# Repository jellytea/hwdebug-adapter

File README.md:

# hwdebug-adapter
Adapter for various debug ports.

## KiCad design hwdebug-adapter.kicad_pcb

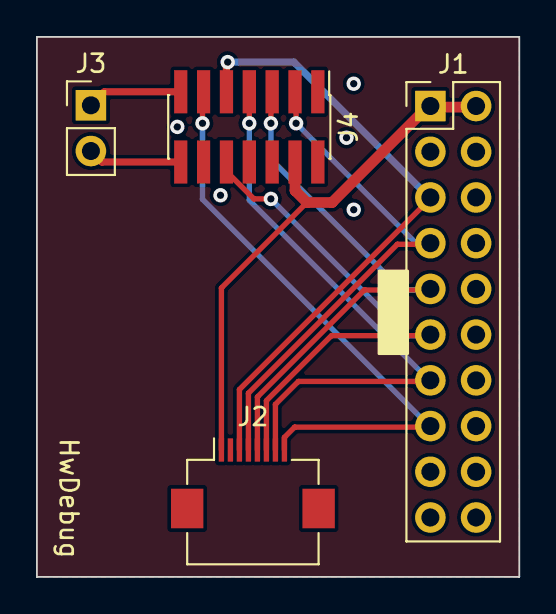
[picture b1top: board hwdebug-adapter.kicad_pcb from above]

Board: 2 copper layers, 26.8 x 30.0 mm, 4 parts (0 on the bottom side), 10 nets.

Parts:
J1: Conn_ARM_JTAG_SWD_20; PinHeader_2x10_P2.54mm_Vertical
J2: Conn_01x08_MountingPin; Hirose_FH12-8S-0.5SH_1x08-1MP_P0.50mm_Horizontal
J3: Conn_01x02; PinHeader_1x02_P2.54mm_Vertical
J4: Conn_ST_STDC14; PinHeader_2x07_P1.27mm_Vertical_SMD

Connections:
+3V3: J1.1 (VTREF), J1.2 (VCC/NC), J2.1, J4.3 (VCC)
GND: J1.4 (GND), J1.6 (GND), J1.8 (GND), J1.10 (GND), J1.12 (GND), J1.14 (GND), J1.16 (GND), J1.18 (GND), J1.20 (GND), J2.2, J2.MP (MountPin), J4.5 (GND), J4.7 (GND), J4.11 (GNDDetect)
unnamed: J1.11 (RTCK), J2.6, J4.9 (JRCLK/NC)
unnamed: J1.9 (TCK/SWCLK), J2.5, J4.6 (JCLK/SWCLK)
unnamed: J1.5 (TDI), J2.3, J4.10 (JTDI/NC)
unnamed: J1.13 (TDO/SWO), J2.7, J4.8 (JTDO/SWO)
unnamed: J1.7 (TMS/SWDIO), J2.4, J4.4 (JTMS/SWDIO)
unnamed: J1.15 (~SRST), J2.8, J4.12 (~RST)
unnamed: J3.1, J4.13 (VCP_RX)
unnamed: J3.2, J4.14 (VCP_TX)

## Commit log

2024-01-28 Revision 1.0

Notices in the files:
hwdebug-adapter.kicad_pcb:
https://creativecommons.org/licenses/by-sa/4.0/legalcode.en
Use of this PCB design is governed under the CC BY-SA 4.0 International license.
© 2024 JetERA Creative
B.SilkS
